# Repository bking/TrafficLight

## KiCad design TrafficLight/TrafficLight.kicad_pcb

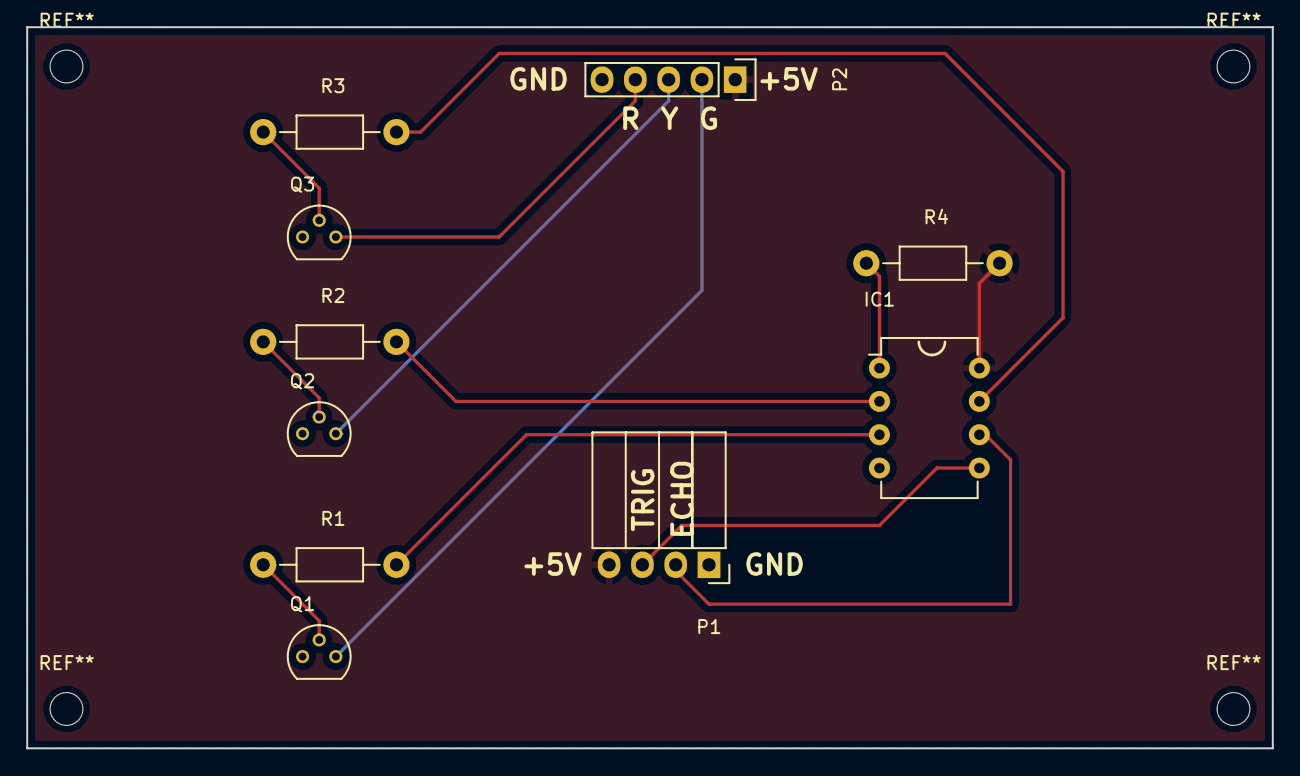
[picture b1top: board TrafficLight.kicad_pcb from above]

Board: 2 copper layers, 95.0 x 55.0 mm, 10 parts (0 on the bottom side), 14 nets.

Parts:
IC1: ATTINY85-P; DIP-8_W7.62mm
P1: HC-SR04 Header; Socket_Strip_Angled_1x04
P2: LED and Power Header; Pin_Header_Straight_1x05
Q1, Q2, Q3: PN2222A; TO-92_Molded_Narrow
R1, R2, R3, R4: R; Resistor_Horizontal_RM10mm

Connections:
+5V: IC1.8, P1.4, P2.1, R4.2
/ECHO: IC1.6, P1.2
/GREEN: IC1.3, R1.2
/RED: IC1.7, R3.2
/TRIG: IC1.5, P1.3
/YELLOW: IC1.2, R2.2
GND: IC1.4, P1.1, P2.5, Q1.1, Q2.1, Q3.1
unnamed: IC1.1, R4.1
unnamed: P2.2, Q1.3
unnamed: P2.3, Q2.3
unnamed: P2.4, Q3.3
unnamed: Q1.2, R1.1
unnamed: Q2.2, R2.1
unnamed: Q3.2, R3.1

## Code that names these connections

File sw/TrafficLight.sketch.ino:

const int TRIG = PB0;
const int ECHO = PB1;
const int RED = PB2;
const int YELLOW = PB3;
const int GREEN = PB4;

// Max time to spend reading the sensor
const unsigned long READ_MAX_DURATION_MS = 60;
// How often to check for movement in checking mode
const unsigned long CHECK_INTERVAL_MS = 1000; 
// How much movement do we consider movement? Has to be more than this:
const unsigned long THRESHOLD_CM = 5;
// How long before we turn off the lights after not detecting movement?
const unsigned long TIMEOUT_MS = 30000;

const int DISTANCE_GREEN = 60;
const int DISTANCE_YELLOW = 80;
const int DISTANCE_RED=50;

enum Mode {
  Checking,
  Tracking
};

Mode __mode = Checking;

unsigned long __trackingTime = 0;
int __lastColor = -1;

void setup() {
  // Serial.begin(115200);
  
  // Pin modes
  pinMode(TRIG, OUTPUT);
  pinMode(ECHO, INPUT);
  pinMode(RED, OUTPUT);
  pinMode(YELLOW, OUTPUT);
  pinMode(GREEN, OUTPUT);

  // Turn off all the LEDs
  digitalWrite(RED, 0);
  digitalWrite(YELLOW, 0);
  digitalWrite(GREEN, 0);

  // Default trigger state is low
  digitalWrite(TRIG, 0);
  // Serial.println("Init complete");
  doTracking();
}

// Returns the measured distance in cm, or -1 if nothing could be read.
int measure()
{
  // Serial.println("M1");
  // To measure, we bring TRIG high for 10us, then wait for ECHO to go high and time it.
  // The distance measured is time(us)/58cm or time(us)/148in. The suggested measurement 
  // cycle is over 60ms.
  digitalWrite(TRIG, 1);
  delayMicroseconds(10);
  digitalWrite(TRIG, 0);

  // Now we wait up to 60ms for the echo pulse
  unsigned long startTime = millis();
  while (millis() - startTime < READ_MAX_DURATION_MS && digitalRead(ECHO) == 0);
  // Serial.println("M2");

  // Did we time out?
  if (digitalRead(ECHO) == 0)
  {
    // Serial.println("TO1");
    return -1;
  }

  unsigned long tStart = micros();
  while (millis() - startTime < READ_MAX_DURATION_MS && digitalRead(ECHO) == 1);
  unsigned long duration = micros() - tStart;
  
  // Did we time out?
  if (digitalRead(ECHO) == 1)
  {
    // Serial.println("TO2");
    return -1;
  }

  // Serial.println(duration / 58);
  return duration / 58;
}

unsigned long __checkingTime = 0;
int __lastMeasurement = -1;
void doChecking()
{
  digitalWrite(RED, 0);
  digitalWrite(GREEN, 0);
  digitalWrite(YELLOW, 0);

  if (millis() - __checkingTime > CHECK_INTERVAL_MS)
  {
    
    __checkingTime = millis();
    // We're looking to see if there is any movement.
    int measurement = measure();
    // Serial.print("M: ");
    // Serial.println(measurement);
    if (measurement == -1)
    {
      return;
    }
    
    if (abs(measurement - __lastMeasurement) > THRESHOLD_CM)
    {
      __lastMeasurement = measurement;
      __mode = Tracking;
    }
  } 
}


void doTracking()
{
  bool moving = false;
  int distance = measure();
  if (distance == -1 || abs(distance - __lastMeasurement) > THRESHOLD_CM) {
    moving = true;
    __trackingTime = millis();
  }
  __lastMeasurement = distance;
  
  if (moving) {
    
    digitalWrite(RED, 0);
    digitalWrite(GREEN, 0);
    digitalWrite(YELLOW, 0);

    if (distance > DISTANCE_YELLOW) {
      digitalWrite(YELLOW, 1);
      if (__lastColor != YELLOW) {
        __lastColor = YELLOW;
      }
    } else if (distance > DISTANCE_GREEN) {
      digitalWrite(GREEN, 1);
      if (__lastColor != GREEN) {
        __lastColor = GREEN;
      }
    } else {
      digitalWrite(RED, 1);
      if (__lastColor != RED) {
        __lastColor = RED;
      }
    }
  }

  if (millis() - __trackingTime > TIMEOUT_MS) {
    __lastColor = -1;
    __mode = Checking;
  }
}

void loop() {
  switch(__mode)
  {
    case Checking:
    doChecking();
    break;

    case Tracking:
    // Serial.print("T");
    doTracking();
    break;
  }
}

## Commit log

2018-07-31 Fix up PCB layout, fix directory names
